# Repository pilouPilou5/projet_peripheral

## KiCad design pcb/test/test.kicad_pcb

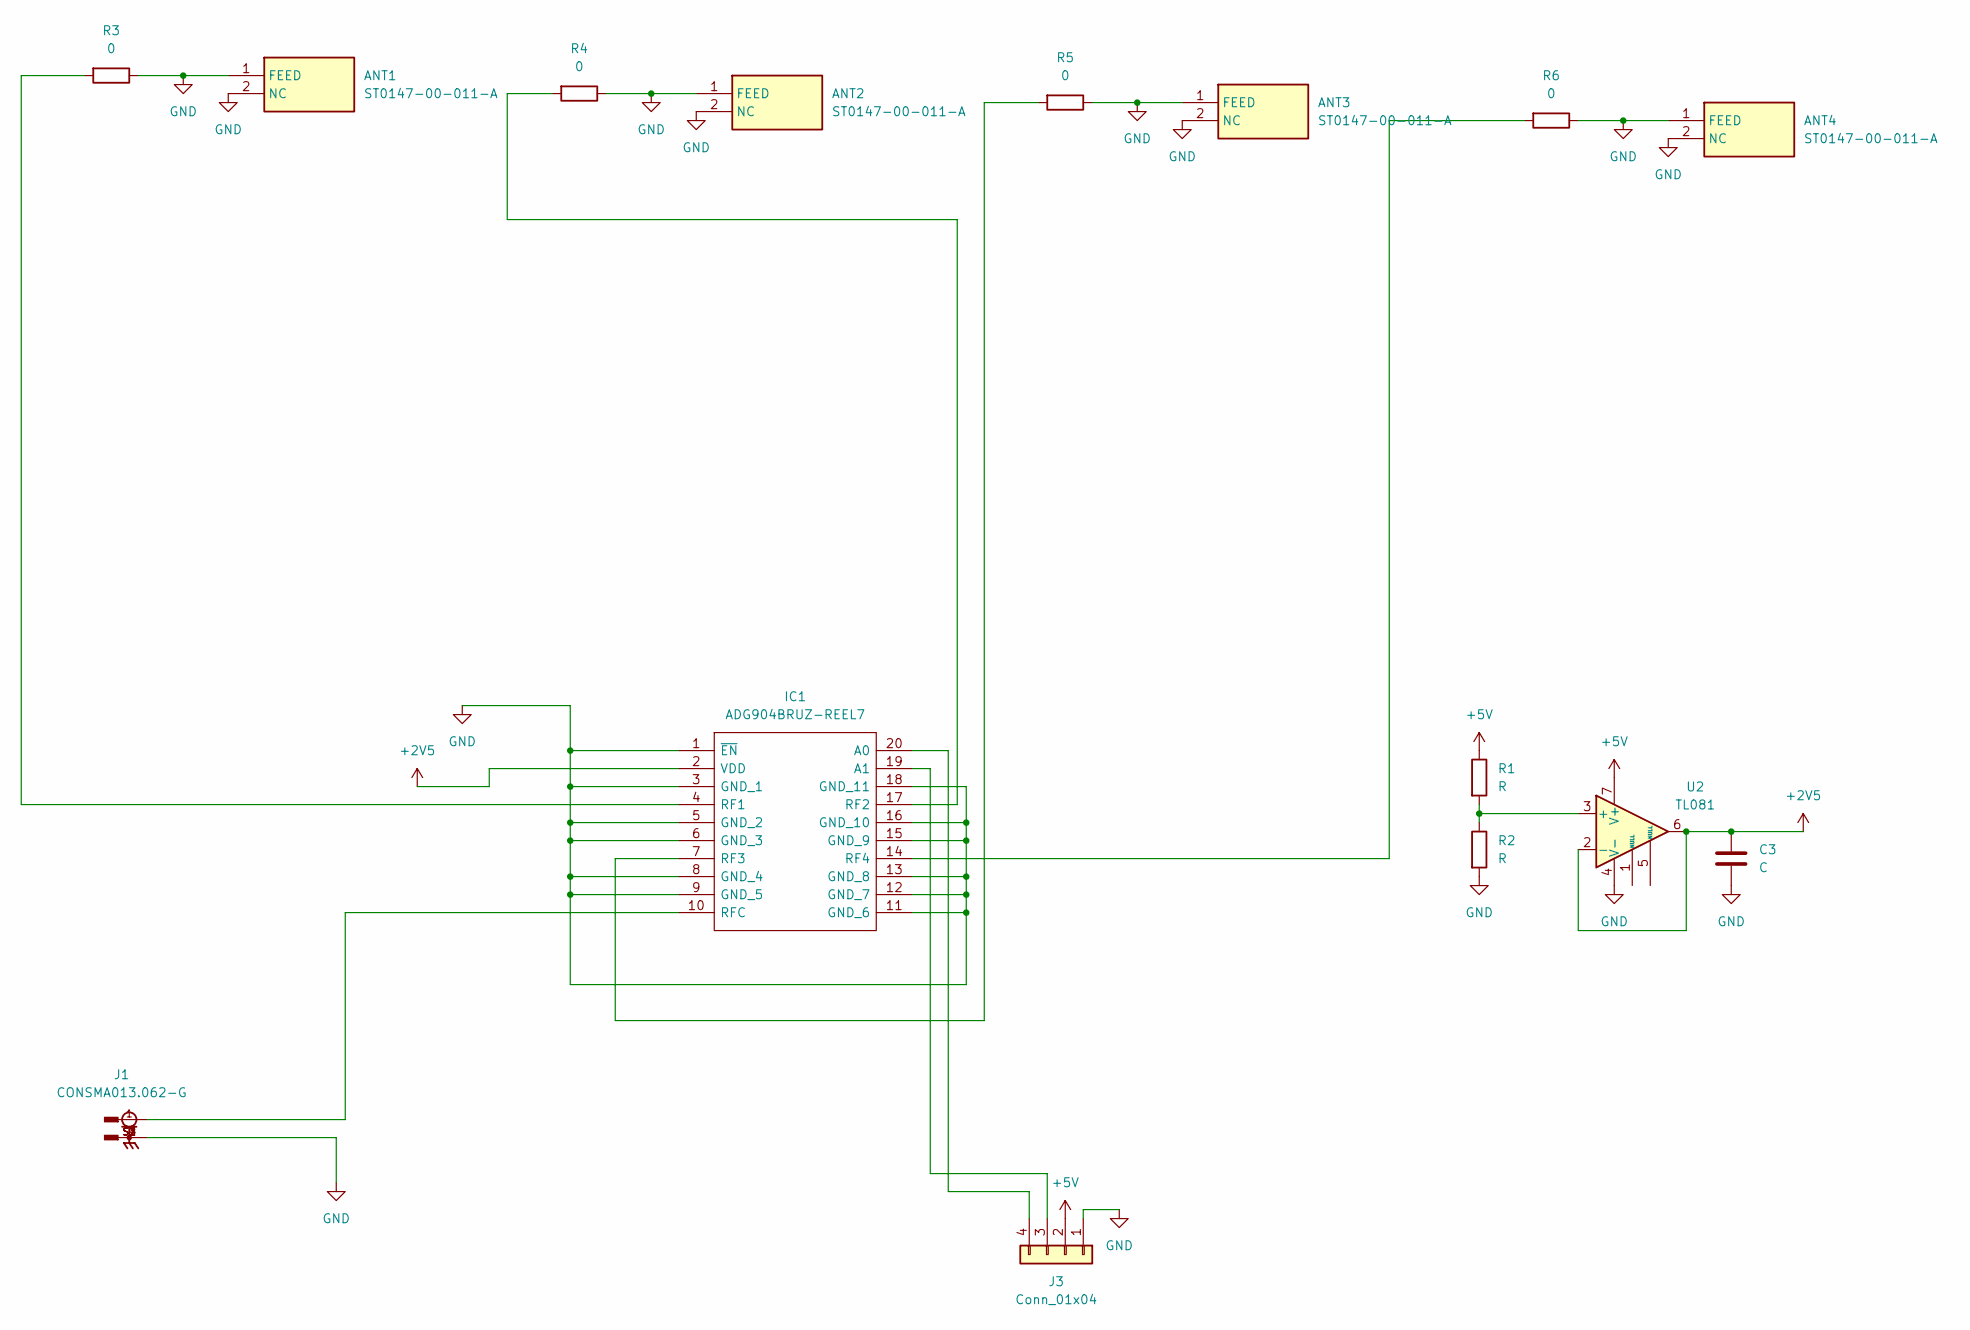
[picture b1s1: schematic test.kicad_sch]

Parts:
ANT1, ANT2, ANT3, ANT4: ST0147-00-011-A; ANTC3016X55N; Manufacturer_Part_Number ST0147-00-011-A
C3: C; CP_Radial_D8.0mm_P5.00mm
IC1: ADG904BRUZ-REEL7; SOP65P640X120-20N; Mouser Part Number 584-ADG904BRUZ-R7
J1: CONSMA013.062-G; LINX_CONSMA013.062-G; PARTREV A
J3: Conn_01x04; PinHeader_1x04_P2.54mm_Horizontal
R1, R2: R; R_Axial_DIN0411_L9.9mm_D3.6mm_P15.24mm_Horizontal
R3, R4, R5, R6: 0; R_0201_0603Metric
U2: TL081; DIP-8_W7.62mm

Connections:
+2V5: C3.1, IC1.2 (VDD), U2.2 (-), U2.6
+5V: J3.2, R1.1, U2.7 (V+)
GND: ANT1.1 (FEED), ANT1.2 (NC), ANT2.1 (FEED), ANT2.2 (NC), ANT3.1 (FEED), ANT3.2 (NC), ANT4.1 (FEED), ANT4.2 (NC), C3.2, IC1.1 (~EN), IC1.3 (GND_1), IC1.5 (GND_2), IC1.6 (GND_3), IC1.8 (GND_4), IC1.9 (GND_5), IC1.11 (GND_6), IC1.12 (GND_7), IC1.13 (GND_8), IC1.15 (GND_9), IC1.16 (GND_10), IC1.18 (GND_11), J1.S1, J1.S2, J1.S3, J1.S4, J3.1, R2.2, R3.1, R4.1, R5.1, R6.1, U2.4 (V-)
unnamed: IC1.20 (A0), J3.4
unnamed: IC1.19 (A1), J3.3
unnamed: IC1.4 (RF1), R3.2
unnamed: IC1.17 (RF2), R4.2
unnamed: IC1.7 (RF3), R5.2
unnamed: IC1.14 (RF4), R6.2
unnamed: IC1.10 (RFC), J1.1
unnamed: R1.2, R2.1, U2.3 (+)

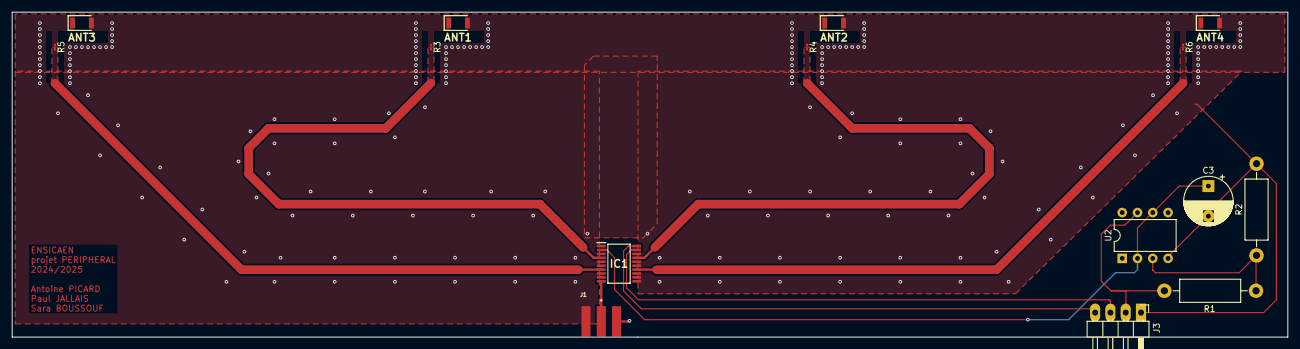
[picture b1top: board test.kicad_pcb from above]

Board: 2 copper layers, 212.0 x 54.0 mm, 15 parts (0 on the bottom side), 11 nets.

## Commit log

2024-12-10 init
2024-12-10 created kicad project and added schematics
2024-12-10 first schematic
2024-12-11 j'ai oublié ce que j'ai fait
2024-12-17 schematic finished ?
2024-12-17 empreintes
2024-12-17 composants placés sur pcb
2024-12-17 pistes
2024-12-18 séance 18/12
2024-12-18 first sofware rx and tx
2024-12-18 update rx firmware
2025-01-02 circuit adaptation impédance
2025-01-05 je commence à comprendre comment les zones fonctionnent
2025-01-07 routage guides d'onde
2025-01-07 aaaaaaaah
2025-01-08 composants pour 2V5 placés
2025-01-08 beaucoup vias
2025-01-08 céfini
2025-01-08 ajustement pour impression
2025-01-09 pcb final
2025-01-13 cleaning
    files are where they were meant to be now
2025-01-13 creation of function estimation of theta
2025-01-15 new test project for manage gpio with switch
2025-01-17 update software test
2025-01-17 fix angle calculation
2025-01-17 abandon
2025-01-22 trying to understand the phase differences
2025-02-03 céfini jabandonne
2025-02-07 final schematics
2025-02-07 mesure angle 2 antennes
2025-02-10 clean
2025-02-12 ajout tuto, rapport et diapo de soutenance
